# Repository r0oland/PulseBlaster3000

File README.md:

# PulseBlaster3000
Custom, teensy based trigger board for various outputs

## Why the name?

In memory of the good old, "PulseBlaster" TTL Pulse Generator we used before, which was total overkill for what we did but worked quite nicely. Thank you SpinCore!
https://www.spincore.com/products/PulseBlaster/

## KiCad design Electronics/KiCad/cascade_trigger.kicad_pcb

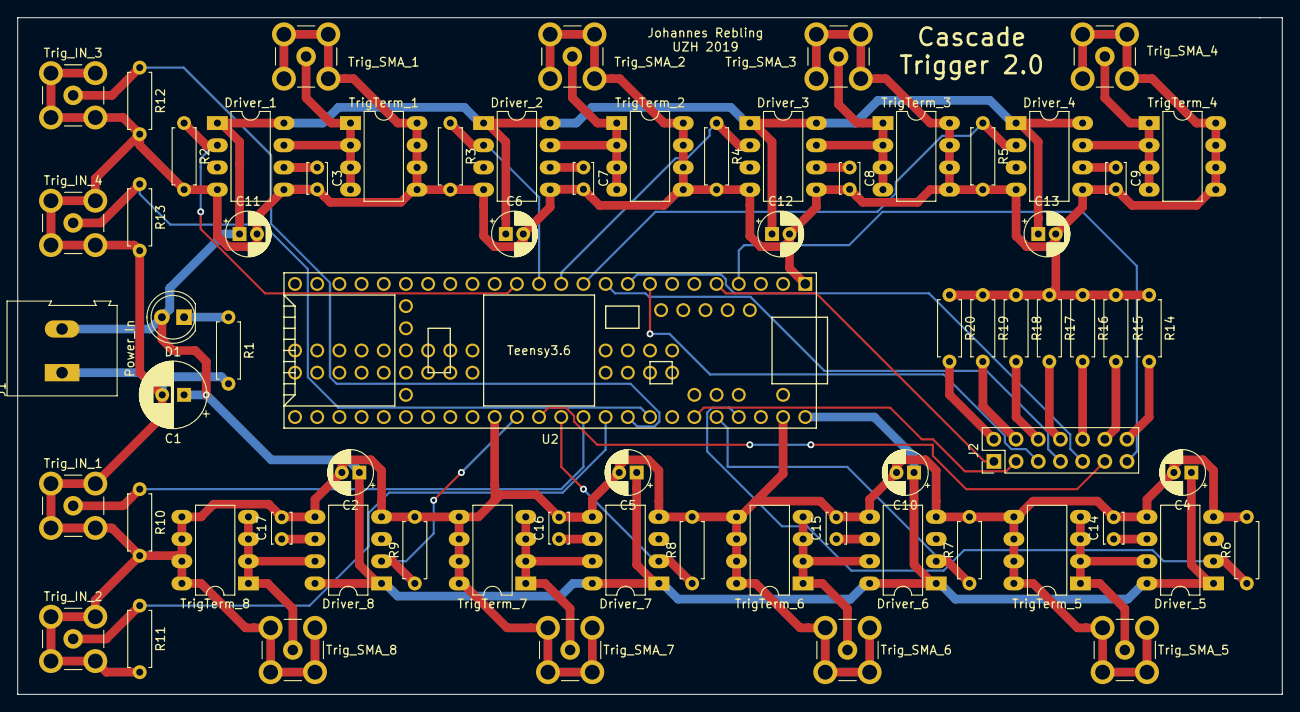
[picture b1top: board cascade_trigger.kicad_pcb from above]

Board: 2 copper layers, 144.8 x 77.5 mm, 69 parts (0 on the bottom side), 45 nets.

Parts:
C1: 100uF; CP_Radial_D7.5mm_P2.50mm
C2, C4, C5, C6, C10, C11, C12, C13: 4.7uF; CP_Radial_D5.0mm_P2.00mm
C3, C7, C8, C9, C14, C15, C16, C17: 2nF; C_Disc_D3.4mm_W2.1mm_P2.50mm
D1: PWR_LED; LED_D5.0mm
Driver_1, Driver_2, Driver_3, Driver_4, Driver_5, Driver_6, Driver_7, Driver_8: EL7104; DIP-8_W7.62mm_LongPads
J1: Power_In; TerminalBlock_Altech_AK300-2_P5.00mm
J2: Conn_02x07_Odd_Even; PinHeader_2x07_P2.54mm_Vertical
R1, R14, R15, R16, R17, R18, R19, R20: 56; R_Axial_DIN0207_L6.3mm_D2.5mm_P7.62mm_Horizontal
R2, R3, R4, R5, R6, R7, R8, R9, R10, R11, R12, R13: 10k; R_Axial_DIN0207_L6.3mm_D2.5mm_P7.62mm_Horizontal
TrigTerm_1, TrigTerm_2, TrigTerm_3, TrigTerm_4, TrigTerm_5, TrigTerm_6, TrigTerm_7, TrigTerm_8: Trig1_Term; DIP-8_W7.62mm_LongPads
Trig_IN_1, Trig_IN_2, Trig_IN_3, Trig_IN_4: Trig_SMA; SMB_Jack_Vertical
Trig_SMA_1, Trig_SMA_2, Trig_SMA_3, Trig_SMA_4, Trig_SMA_5, Trig_SMA_6, Trig_SMA_7, Trig_SMA_8: Trig_SMA; SMB_Jack_Vertical
U2: Teensy3.6; Teensy35_36

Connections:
DrvIn1: Driver_1.2, R2.1, U2.14
DrvIn2: Driver_2.2, R3.1, U2.13
DrvIn3: Driver_3.2, R4.1, U2.12
DrvIn4: Driver_4.2, R5.1, U2.11
DrvIn5: Driver_5.2, R6.1, U2.50
DrvIn6: Driver_6.2, R7.1, U2.49
DrvIn7: Driver_7.2, R8.1, U2.42
DrvIn8: Driver_8.2, R9.1, U2.40
GND: C1.2, C2.2, C3.2, C4.2, C5.2, C6.2, C7.2, C8.2, C9.2, C10.2, C11.2, C12.2, C13.2, C14.2, C15.2, C16.2, C17.2, Driver_1.4, Driver_1.5, Driver_2.4, Driver_2.5, Driver_3.4, Driver_3.5, Driver_4.4, Driver_4.5, Driver_5.4, Driver_5.5, Driver_6.4, Driver_6.5, Driver_7.4, Driver_7.5, Driver_8.4, Driver_8.5, J1.1, R1.2, R2.2, R3.2, R4.2, R5.2, R6.2, R7.2, R8.2, R9.2, R10.2, R11.2, R12.2, R13.2, R14.1, R15.1, R16.1, R17.1, R18.1, R19.1, R20.1, TrigTerm_1.5, TrigTerm_1.6, TrigTerm_1.7, TrigTerm_1.8, TrigTerm_2.5, TrigTerm_2.6, TrigTerm_2.7, TrigTerm_2.8, TrigTerm_3.5, TrigTerm_3.6, TrigTerm_3.7, TrigTerm_3.8, TrigTerm_4.5, TrigTerm_4.6, TrigTerm_4.7, TrigTerm_4.8, TrigTerm_5.5, TrigTerm_5.6, TrigTerm_5.7, TrigTerm_5.8, TrigTerm_6.5, TrigTerm_6.6, TrigTerm_6.7, TrigTerm_6.8, TrigTerm_7.5, TrigTerm_7.6, TrigTerm_7.7, TrigTerm_7.8, TrigTerm_8.5, TrigTerm_8.6, TrigTerm_8.7, TrigTerm_8.8, Trig_IN_1.2, Trig_IN_2.2, Trig_IN_3.2, Trig_IN_4.2, Trig_SMA_1.2, Trig_SMA_2.2, Trig_SMA_3.2, Trig_SMA_4.2, Trig_SMA_5.2, Trig_SMA_6.2, Trig_SMA_7.2, Trig_SMA_8.2, U2.1, U2.39, U2.52
LedOut1: J2.1, U2.5
LedOut2: J2.3, U2.48
LedOut3: J2.5, U2.8
LedOut4: J2.7, U2.10
LedOut5: J2.9, U2.9
LedOut6: J2.11, U2.41
LedOut7: J2.13, U2.4
unnamed: C3.1, Driver_1.6
unnamed: C7.1, Driver_2.6
unnamed: C8.1, Driver_3.6
unnamed: C9.1, Driver_4.6
unnamed: C14.1, Driver_5.6
unnamed: C15.1, Driver_6.6
unnamed: C16.1, Driver_7.6
unnamed: C17.1, Driver_8.6
unnamed: D1.1, R1.1
unnamed: Driver_1.7, TrigTerm_1.1, TrigTerm_1.2, TrigTerm_1.3, TrigTerm_1.4, Trig_SMA_1.1
unnamed: Driver_2.7, TrigTerm_2.1, TrigTerm_2.2, TrigTerm_2.3, TrigTerm_2.4, Trig_SMA_2.1
unnamed: Driver_3.7, TrigTerm_3.1, TrigTerm_3.2, TrigTerm_3.3, TrigTerm_3.4, Trig_SMA_3.1
unnamed: Driver_4.7, TrigTerm_4.1, TrigTerm_4.2, TrigTerm_4.3, TrigTerm_4.4, Trig_SMA_4.1
unnamed: Driver_5.7, TrigTerm_5.1, TrigTerm_5.2, TrigTerm_5.3, TrigTerm_5.4, Trig_SMA_5.1
unnamed: Driver_6.7, TrigTerm_6.1, TrigTerm_6.2, TrigTerm_6.3, TrigTerm_6.4, Trig_SMA_6.1
unnamed: Driver_7.7, TrigTerm_7.1, TrigTerm_7.2, TrigTerm_7.3, TrigTerm_7.4, Trig_SMA_7.1
unnamed: Driver_8.7, TrigTerm_8.1, TrigTerm_8.2, TrigTerm_8.3, TrigTerm_8.4, Trig_SMA_8.1
unnamed: J2.2, R20.2
unnamed: J2.4, R19.2
unnamed: J2.6, R18.2
unnamed: J2.8, R17.2
unnamed: J2.10, R16.2
unnamed: J2.12, R15.2
unnamed: J2.14, R14.2
TrigIn1: R10.1, Trig_IN_1.1, U2.43
TrigIn2: R11.1, Trig_IN_2.1, U2.44
TrigIn3: R12.1, Trig_IN_3.1, U2.45
TrigIn4: R13.1, Trig_IN_4.1, U2.46
VCC: C1.1, C2.1, C4.1, C5.1, C6.1, C10.1, C11.1, C12.1, C13.1, D1.2, Driver_1.1, Driver_1.8, Driver_2.1, Driver_2.8, Driver_3.1, Driver_3.8, Driver_4.1, Driver_4.8, Driver_5.1, Driver_5.8, Driver_6.1, Driver_6.8, Driver_7.1, Driver_7.8, Driver_8.1, Driver_8.8, J1.2, U2.53

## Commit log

2020-06-04 adding firmware, kicad and matlab files
2020-06-05 orga + fixing init trigger bug
2020-06-08 update trigger
2020-06-17 trying to unify trigger
2020-06-17 clean start + auto firmware update
2020-06-17 clean up and separate chen
2020-06-17 simple scope working
2020-06-17 Removed submodule Matlab_Failed/submodules/BHC
2020-06-17 Removed submodule Matlab_Failed/submodules/MatlabUtilities
2020-06-17 Removed submodule Matlab_Failed/submodules/Mex_C_Serial_Interface
2020-06-25 before switch to teensy 41
2020-06-25 compiling for t36
2020-07-16 remove older files, fixed LMI bug, renamed LMI functions
2020-07-29 updating examples
2020-07-31 more flexible serial port handling
2020-08-05 change to Obj. and make serial in matlab variable
2020-08-18 adding led strip support
2020-08-19 adding simple cascade trigger (based on quad signal) back
2020-08-19 updating matlab code to match new firmware
2020-08-20 adding mode for legacy
2020-09-02 updated utils
2020-10-22 remove redundandt submodules
2020-10-27 targeted teensy uploads + easy restart
2020-10-30 update cascade to include trigger duration + minor fixes
2020-11-05 check connection during init
2020-11-08 moved mex-c here, as this is last repo to actually use it...
